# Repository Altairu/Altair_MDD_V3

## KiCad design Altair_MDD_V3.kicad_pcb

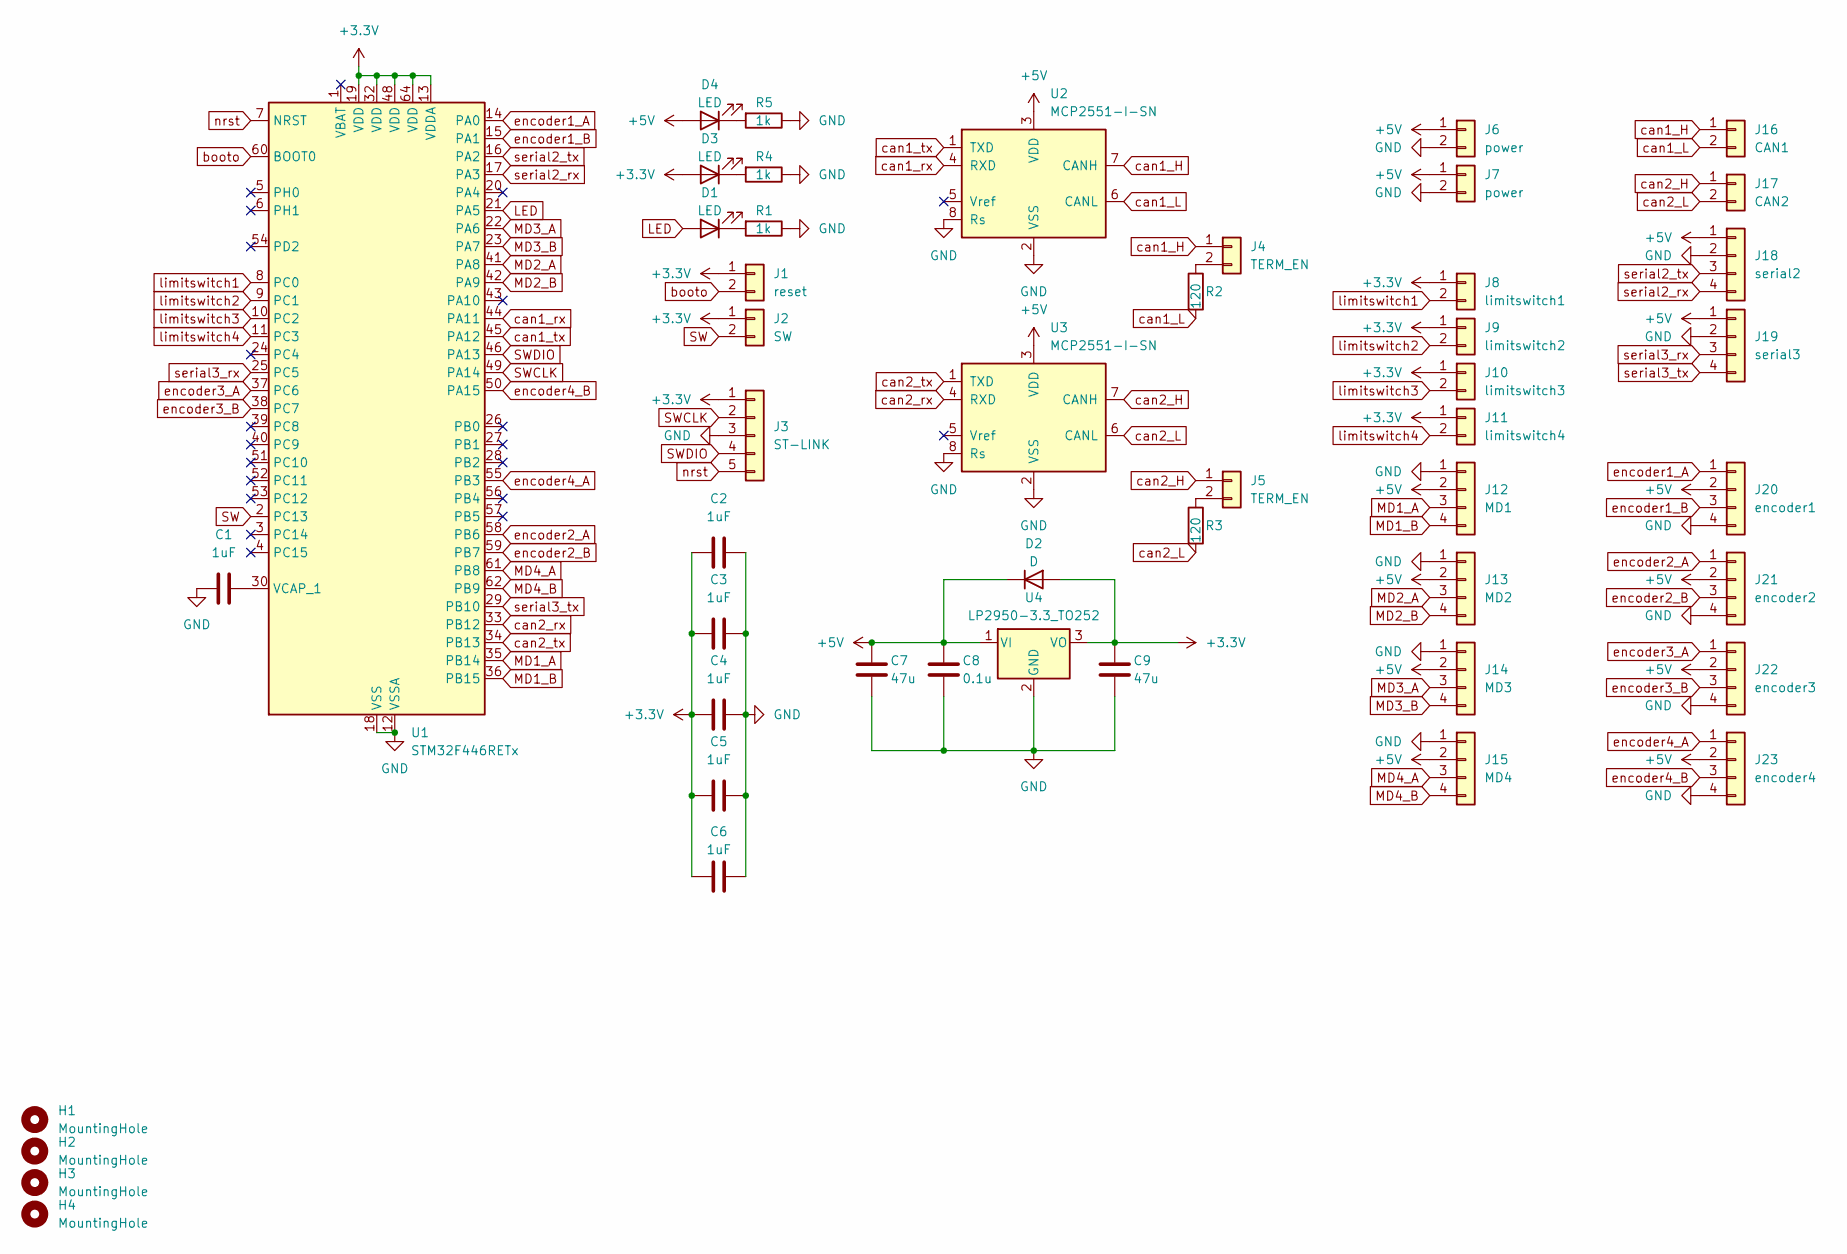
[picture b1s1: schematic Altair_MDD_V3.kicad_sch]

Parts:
C1, C2, C3, C4, C5, C6: 1uF; C_0603_1608Metric
C7, C9: 47u; C_0603_1608Metric
C8: 0.1u; C_0603_1608Metric
D1, D3, D4: LED; LED_0603_1608Metric
D2: D; D_0603_1608Metric
H1, H2, H3, H4: MountingHole; MountingHole_3.2mm_M3_Pad_Via
J1: reset; PinSocket_1x02_P2.54mm_Vertical
J2: SW; PinSocket_1x02_P2.54mm_Vertical
J3: ST-LINK; PinSocket_1x05_P2.54mm_Vertical
J4, J5: TERM_EN; PinSocket_1x02_P2.54mm_Vertical
J6, J7: power; JST_XA_S02B-XASK-1_1x02_P2.50mm_Horizontal
J8: limitswitch1; JST_XA_S02B-XASK-1_1x02_P2.50mm_Horizontal
J9: limitswitch2; JST_XA_S02B-XASK-1_1x02_P2.50mm_Horizontal
J10: limitswitch3; JST_XA_S02B-XASK-1_1x02_P2.50mm_Horizontal
J11: limitswitch4; JST_XA_S02B-XASK-1_1x02_P2.50mm_Horizontal
J12: MD1; JST_XA_S04B-XASK-1_1x04_P2.50mm_Horizontal
J13: MD2; JST_XA_S04B-XASK-1_1x04_P2.50mm_Horizontal
J14: MD3; JST_XA_S04B-XASK-1_1x04_P2.50mm_Horizontal
J15: MD4; JST_XA_S04B-XASK-1_1x04_P2.50mm_Horizontal
J16: CAN1; JST_XA_S02B-XASK-1_1x02_P2.50mm_Horizontal
J17: CAN2; JST_XA_S02B-XASK-1_1x02_P2.50mm_Horizontal
J18: serial2; JST_XA_B04B-XASK-1-A_1x04_P2.50mm_Vertical
J19: serial3; JST_XA_B04B-XASK-1-A_1x04_P2.50mm_Vertical
J20: encoder1; JST_XA_S04B-XASK-1_1x04_P2.50mm_Horizontal
J21: encoder2; JST_XA_S04B-XASK-1_1x04_P2.50mm_Horizontal
J22: encoder3; JST_XA_S04B-XASK-1_1x04_P2.50mm_Horizontal
J23: encoder4; JST_XA_S04B-XASK-1_1x04_P2.50mm_Horizontal
R1, R4, R5: 1k; R_0603_1608Metric
R2, R3: 120; R_0603_1608Metric
U1: STM32F446RETx; LQFP-64_10x10mm_P0.5mm
U2, U3: MCP2551-I-SN; SOIC-8_3.9x4.9mm_P1.27mm
U4: LP2950-3.3_TO252; TO-252-2

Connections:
+3.3V: C2.1, C3.1, C4.1, C5.1, C6.1, C9.1, D2.2 (A), D3.2 (A), J1.1, J2.1, J3.1, J8.1, J9.1, J10.1, J11.1, U1.13 (VDDA), U1.19 (VDD), U1.32 (VDD), U1.48 (VDD), U1.64 (VDD), U4.3 (VO)
+5V: C7.1, C8.1, D2.1 (K), D4.2 (A), J6.1, J7.1, J12.2, J13.2, J14.2, J15.2, J18.1, J19.1, J20.2, J21.2, J22.2, J23.2, U2.3 (VDD), U3.3 (VDD), U4.1 (VI)
GND: C1.1, C2.2, C3.2, C4.2, C5.2, C6.2, C7.2, C8.2, C9.2, J3.3, J6.2, J7.2, J12.1, J13.1, J14.1, J15.1, J18.2, J19.2, J20.4, J21.4, J22.4, J23.4, R1.1, R4.1, R5.1, U1.12 (VSSA), U1.18 (VSS), U1.31 (VSS), U1.47 (VSS), U1.63 (VSS), U2.2 (VSS), U2.8 (Rs), U3.2 (VSS), U3.8 (Rs), U4.2 (GND)
LED: D1.2 (A), U1.21 (PA5)
MD1_A: J12.3, U1.35 (PB14)
MD1_B: J12.4, U1.36 (PB15)
MD2_A: J13.3, U1.41 (PA8)
MD2_B: J13.4, U1.42 (PA9)
MD3_A: J14.3, U1.22 (PA6)
MD3_B: J14.4, U1.23 (PA7)
MD4_A: J15.3, U1.61 (PB8)
MD4_B: J15.4, U1.62 (PB9)
unnamed: D1.1 (K), R1.2
unnamed: D3.1 (K), R4.2
unnamed: D4.1 (K), R5.2
unnamed: J4.2, R2.1
unnamed: J5.2, R3.1
unnamed: C1.2, U1.30 (VCAP_1)
SW: J2.2, U1.2 (PC13)
SWCLK: J3.2, U1.49 (PA14)
SWDIO: J3.4, U1.46 (PA13)
booto: J1.2, U1.60 (BOOT0)
can1_H: J4.1, J16.1, U2.7 (CANH)
can1_L: J16.2, R2.2, U2.6 (CANL)
can1_rx: U1.44 (PA11), U2.4 (RXD)
can1_tx: U1.45 (PA12), U2.1 (TXD)
can2_H: J5.1, J17.1, U3.7 (CANH)
can2_L: J17.2, R3.2, U3.6 (CANL)
can2_rx: U1.33 (PB12), U3.4 (RXD)
can2_tx: U1.34 (PB13), U3.1 (TXD)
encoder1_A: J20.1, U1.14 (PA0)
encoder1_B: J20.3, U1.15 (PA1)
encoder2_A: J21.1, U1.58 (PB6)
encoder2_B: J21.3, U1.59 (PB7)
encoder3_A: J22.1, U1.37 (PC6)
encoder3_B: J22.3, U1.38 (PC7)
encoder4_A: J23.1, U1.55 (PB3)
encoder4_B: J23.3, U1.50 (PA15)
limitswitch1: J8.2, U1.8 (PC0)
limitswitch2: J9.2, U1.9 (PC1)
limitswitch3: J10.2, U1.10 (PC2)
limitswitch4: J11.2, U1.11 (PC3)
nrst: J3.5, U1.7 (NRST)
serial2_rx: J18.4, U1.17 (PA3)
serial2_tx: J18.3, U1.16 (PA2)
serial3_rx: J19.3, U1.25 (PC5)
serial3_tx: J19.4, U1.29 (PB10)

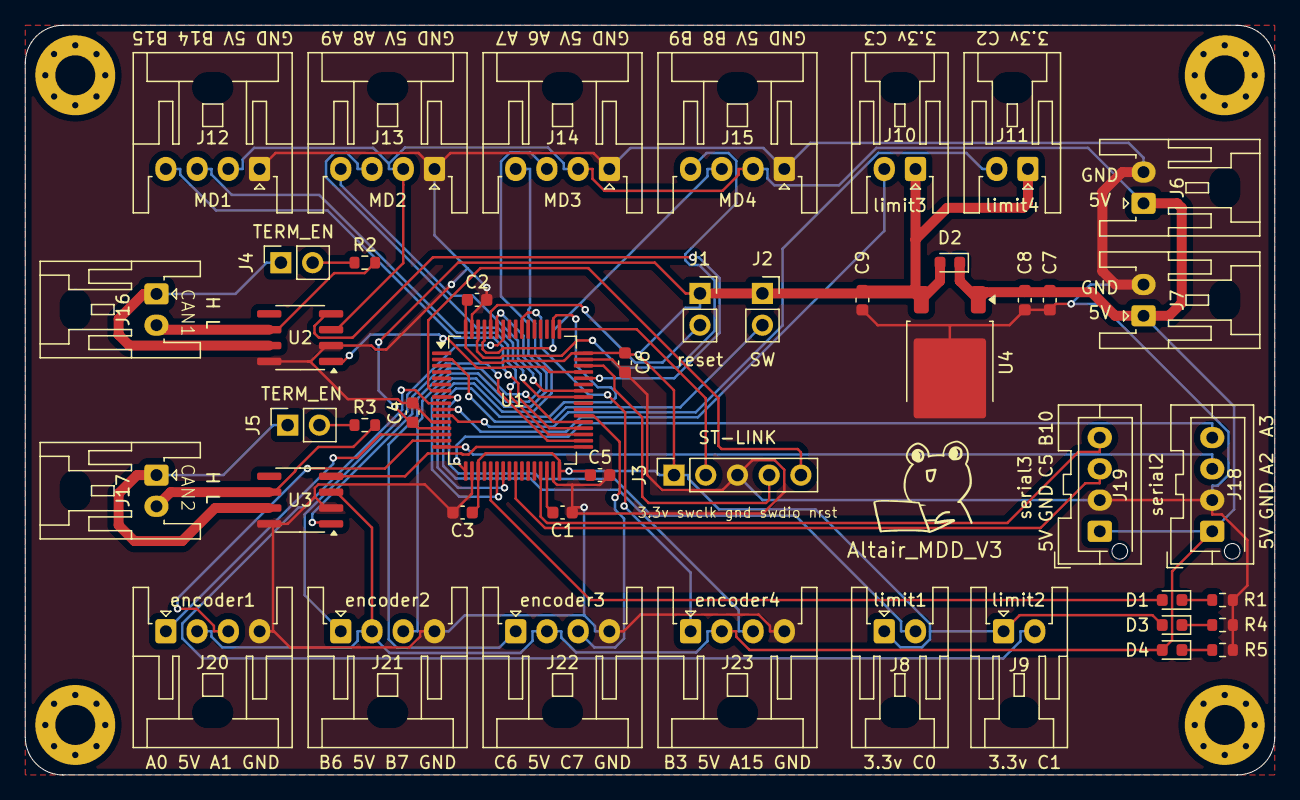
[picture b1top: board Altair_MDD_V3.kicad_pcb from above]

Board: 2 copper layers, 100.0 x 60.0 mm, 49 parts (0 on the bottom side), 47 nets.

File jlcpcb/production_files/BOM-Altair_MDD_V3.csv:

Comment,Designator,Footprint,LCSC,Quantity
0.1u,C8,C_0603_1608Metric,C125205,1
LP2950-3.3_TO252,U4,TO-252-2,C129994,1
47u,"C7,C9",C_0603_1608Metric,C140782,2
120,"R2,R3",R_0603_1608Metric,C14709,2
1uF,"C1,C2,C3,C4,C5,C6",C_0603_1608Metric,C1592,6
LED,"D1,D3,D4",LED_0603_1608Metric,C2290,3
D,D2,D_0603_1608Metric,C3758192,1
STM32F446RETx,U1,LQFP-64_10x10mm_P0.5mm,C69336,1
MCP2551-I-SN,"U2,U3",SOIC-8_3.9x4.9mm_P1.27mm,C7376,2
1k,"R1,R4,R5",R_0603_1608Metric,C78748,3
MD2,J13,JST_XA_S04B-XASK-1_1x04_P2.50mm_Horizontal,,1
SW,J2,PinSocket_1x02_P2.54mm_Vertical,,1
power,J6,JST_XA_S02B-XASK-1_1x02_P2.50mm_Horizontal,,1
limitswitch4,J11,JST_XA_S02B-XASK-1_1x02_P2.50mm_Horizontal,,1
limitswitch3,J10,JST_XA_S02B-XASK-1_1x02_P2.50mm_Horizontal,,1
encoder1,J20,JST_XA_S04B-XASK-1_1x04_P2.50mm_Horizontal,,1
MD3,J14,JST_XA_S04B-XASK-1_1x04_P2.50mm_Horizontal,,1
MountingHole,H2,MountingHole_3.2mm_M3_Pad_Via,,1
serial2,J18,JST_XA_B04B-XASK-1-A_1x04_P2.50mm_Vertical,,1
encoder4,J23,JST_XA_S04B-XASK-1_1x04_P2.50mm_Horizontal,,1
TERM_EN,J4,PinSocket_1x02_P2.54mm_Vertical,,1
serial3,J19,JST_XA_B04B-XASK-1-A_1x04_P2.50mm_Vertical,,1
reset,J1,PinSocket_1x02_P2.54mm_Vertical,,1
limitswitch2,J9,JST_XA_S02B-XASK-1_1x02_P2.50mm_Horizontal,,1
MD4,J15,JST_XA_S04B-XASK-1_1x04_P2.50mm_Horizontal,,1
MountingHole,H1,MountingHole_3.2mm_M3_Pad_Via,,1
TERM_EN,J5,PinSocket_1x02_P2.54mm_Vertical,,1
encoder2,J21,JST_XA_S04B-XASK-1_1x04_P2.50mm_Horizontal,,1
encoder3,J22,JST_XA_S04B-XASK-1_1x04_P2.50mm_Horizontal,,1
limitswitch1,J8,JST_XA_S02B-XASK-1_1x02_P2.50mm_Horizontal,,1
MountingHole,H4,MountingHole_3.2mm_M3_Pad_Via,,1
CAN2,J17,JST_XA_S02B-XASK-1_1x02_P2.50mm_Horizontal,,1
ST-LINK,J3,PinSocket_1x05_P2.54mm_Vertical,,1
CAN1,J16,JST_XA_S02B-XASK-1_1x02_P2.50mm_Horizontal,,1
MD1,J12,JST_XA_S04B-XASK-1_1x04_P2.50mm_Horizontal,,1
power,J7,JST_XA_S02B-XASK-1_1x02_P2.50mm_Horizontal,,1
MountingHole,H3,MountingHole_3.2mm_M3_Pad_Via,,1
